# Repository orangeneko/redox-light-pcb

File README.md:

## About
Eagle version of PCB for [Redox keyboard](https://github.com/mattdibi/redox-keyboard) with RBG backlight (of each keys).

## PCB

## Hardware
* Cortex M3 STM32F103T8U
* SK6812 CMD 3535 Leds (similar with WS2812B)
* Cherry MX switches
* Kailh PCB sockets

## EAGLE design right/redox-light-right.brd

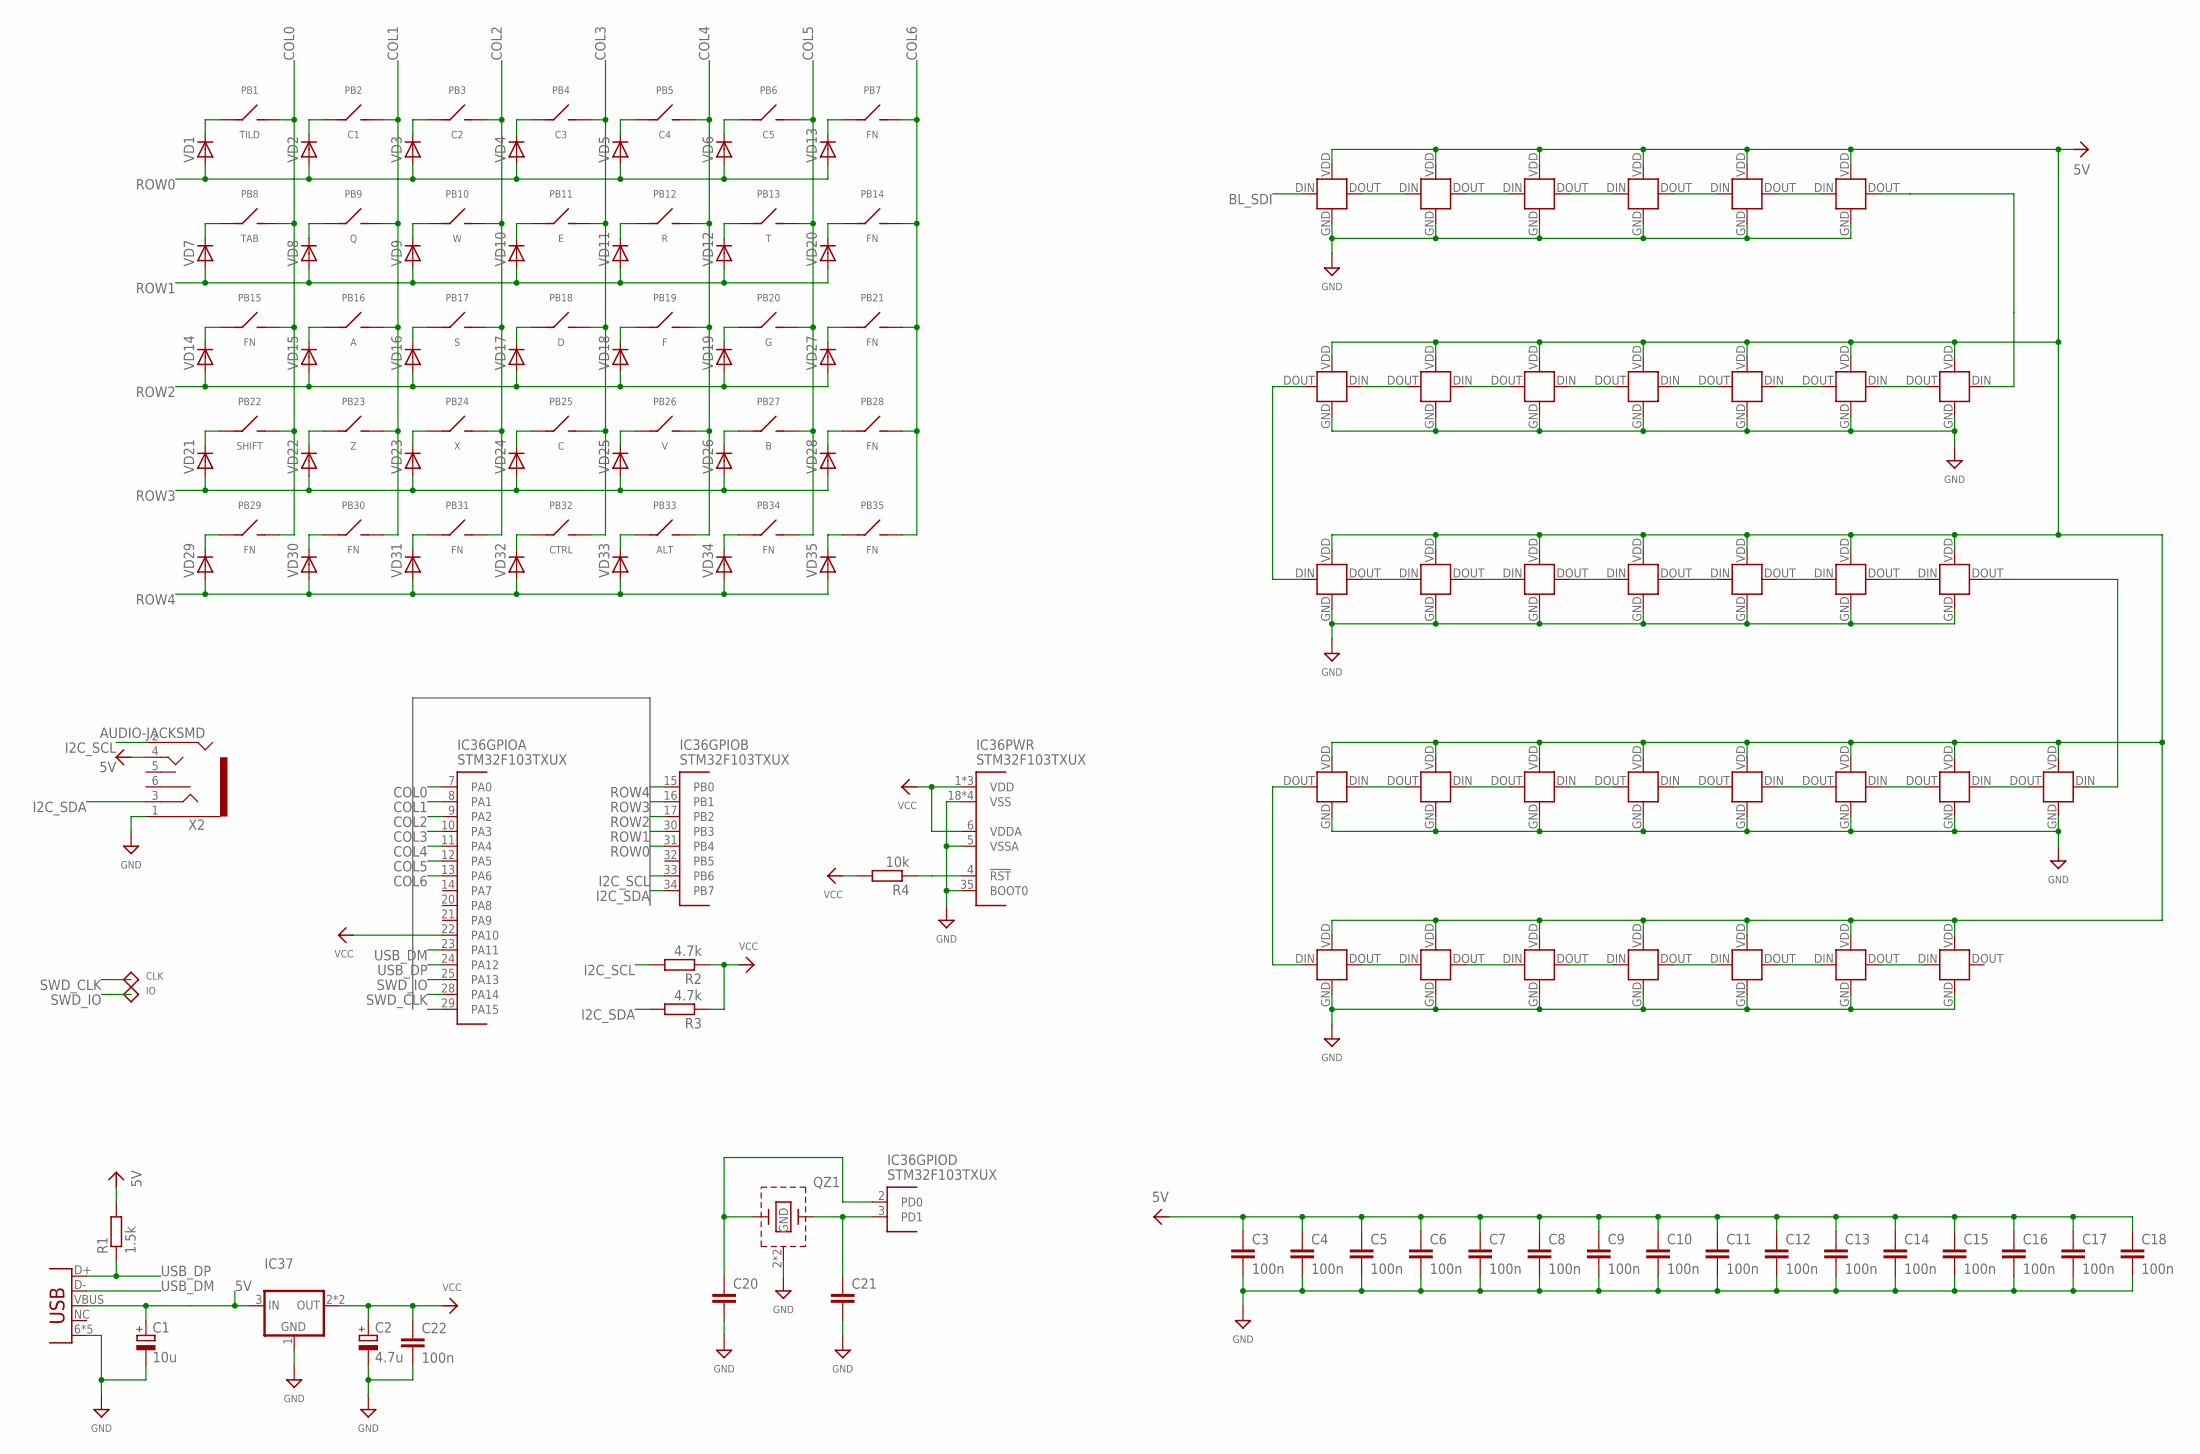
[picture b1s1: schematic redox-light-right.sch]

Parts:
C1: 10u; SMC_A
C2: 4.7u; SMC_A
C3, C4, C5, C6, C7, C8, C9, C10, C11, C12, C13, C14, C15, C16, C17, C18, C22: 100n; R0402
C20, C21: CAP0402; R0402
IC1, IC2, IC3, IC4, IC5, IC6, IC7, IC8, IC9, IC10, IC11, IC12, IC13, IC14, IC15, IC16, IC17, IC18, IC19, IC20, IC21, IC22, IC23, IC24, IC25, IC26, IC27, IC28, IC29, IC30, IC31, IC32, IC33, IC34, IC35: SK68XX-MINI
IC36: STM32F103TXUX; QFN-36
IC37: LM1117; SOT89
PB1: TILD; CHERRY-MX-KAILH
PB2: C1; CHERRY-MX-KAILH
PB3: C2; CHERRY-MX-KAILH
PB4: C3; CHERRY-MX-KAILH
PB5: C4; CHERRY-MX-KAILH
PB6: C5; CHERRY-MX-KAILH
PB7, PB14, PB15, PB21, PB28, PB29, PB30, PB31, PB34, PB35: FN; CHERRY-MX-KAILH
PB8: TAB; CHERRY-MX-KAILH
PB9: Q; CHERRY-MX-KAILH
PB10: W; CHERRY-MX-KAILH
PB11: E; CHERRY-MX-KAILH
PB12: R; CHERRY-MX-KAILH
PB13: T; CHERRY-MX-KAILH
PB16: A; CHERRY-MX-KAILH
PB17: S; CHERRY-MX-KAILH
PB18: D; CHERRY-MX-KAILH
PB19: F; CHERRY-MX-KAILH
PB20: G; CHERRY-MX-KAILH
PB22: SHIFT; CHERRY-MX-KAILH
PB23: Z; CHERRY-MX-KAILH
PB24: X; CHERRY-MX-KAILH
PB25: C; CHERRY-MX-KAILH
PB26: V; CHERRY-MX-KAILH
PB27: B; CHERRY-MX-KAILH
PB32: CTRL; CHERRY-MX-KAILH
PB33: ALT; CHERRY-MX-KAILH
QZ1: QUARTZ_GND3225; 3225
R1: 1.5k; R0402
R2, R3: 4.7k; R0402
R4: 10k; R0402
TP1: CLK; TP10R
TP2: IO; TP10R
VD1, VD2, VD3, VD4, VD5, VD6, VD7, VD8, VD9, VD10, VD11, VD12, VD13, VD14, VD15, VD16, VD17, VD18, VD19, VD20, VD21, VD22, VD23, VD24, VD25, VD26, VD27, VD28, VD29, VD30, VD31, VD32, VD33, VD34, VD35: DIODE-SOD123; SOD123
X1: USBMICRO_B; USB_MICROB
X2: AUDIO-JACKSMD; PJ-342

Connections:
5V: C1.+, C3.1, C4.1, C5.1, C6.1, C7.1, C8.1, C9.1, C10.1, C11.1, C12.1, C13.1, C14.1, C15.1, C16.1, C17.1, C18.1, IC1.VDD (VCC), IC2.VDD (VCC), IC3.VDD (VCC), IC4.VDD (VCC), IC5.VDD (VCC), IC6.VDD (VCC), IC7.VDD (VCC), IC8.VDD (VCC), IC9.VDD (VCC), IC10.VDD (VCC), IC11.VDD (VCC), IC12.VDD (VCC), IC13.VDD (VCC), IC14.VDD (VCC), IC15.VDD (VCC), IC16.VDD (VCC), IC17.VDD (VCC), IC18.VDD (VCC), IC19.VDD (VCC), IC20.VDD (VCC), IC21.VDD (VCC), IC22.VDD (VCC), IC23.VDD (VCC), IC24.VDD (VCC), IC25.VDD (VCC), IC26.VDD (VCC), IC27.VDD (VCC), IC28.VDD (VCC), IC29.VDD (VCC), IC30.VDD (VCC), IC31.VDD (VCC), IC32.VDD (VCC), IC33.VDD (VCC), IC34.VDD (VCC), IC35.VDD (VCC), IC37.3 (IN), R1.2, X1.VBUS, X2.4
BL_SDI: IC1.DIN, IC36.29 (PA15)
COL0: IC36.7 (PA0), PB1.2, PB8.2, PB15.2, PB22.2, PB29.2
COL1: IC36.8 (PA1), PB2.2, PB9.2, PB16.2, PB23.2, PB30.2
COL2: IC36.9 (PA2), PB3.2, PB10.2, PB17.2, PB24.2, PB31.2
COL3: IC36.10 (PA3), PB4.2, PB11.2, PB18.2, PB25.2, PB32.2
COL4: IC36.11 (PA4), PB5.2, PB12.2, PB19.2, PB26.2, PB33.2
COL5: IC36.12 (PA5), PB6.2, PB13.2, PB20.2, PB27.2, PB34.2
COL6: IC36.13 (PA6), PB7.2, PB14.2, PB21.2, PB28.2, PB35.2
GND: C1.-, C2.-, C3.2, C4.2, C5.2, C6.2, C7.2, C8.2, C9.2, C10.2, C11.2, C12.2, C13.2, C14.2, C15.2, C16.2, C17.2, C18.2, C20.2, C21.2, C22.2, IC1.GND, IC2.GND, IC3.GND, IC4.GND, IC5.GND, IC6.GND, IC7.GND, IC8.GND, IC9.GND, IC10.GND, IC11.GND, IC12.GND, IC13.GND, IC14.GND, IC15.GND, IC16.GND, IC17.GND, IC18.GND, IC19.GND, IC20.GND, IC21.GND, IC22.GND, IC23.GND, IC24.GND, IC25.GND, IC26.GND, IC27.GND, IC28.GND, IC29.GND, IC30.GND, IC31.GND, IC32.GND, IC33.GND, IC34.GND, IC35.GND, IC36.5 (VSSA), IC36.18 (VSS), IC36.26 (VSS), IC36.35 (BOOT0), IC36.36 (VSS), IC36.PGND (VSS), IC37.1 (GND), QZ1.2 (GND), QZ1.4 (GND), X1.6 (GND), X1.7 (GND), X1.8 (GND), X1.9 (GND), X1.GND, X2.1
I2C_SCL: IC36.33 (PB6), R2.2, X2.2
I2C_SDA: IC36.34 (PB7), R3.2, X2.3
unnamed: IC1.DOUT, IC2.DIN
unnamed: IC2.DOUT, IC3.DIN
unnamed: IC3.DOUT, IC4.DIN
unnamed: IC4.DOUT, IC5.DIN
unnamed: IC5.DOUT, IC6.DIN
unnamed: IC7.DOUT, IC8.DIN
unnamed: PB1.1, VD1.C
unnamed: IC21.DOUT, IC22.DIN
unnamed: IC22.DOUT, IC23.DIN
unnamed: IC23.DOUT, IC24.DIN
unnamed: IC24.DOUT, IC25.DIN
unnamed: IC25.DOUT, IC26.DIN
unnamed: IC8.DOUT, IC9.DIN
unnamed: IC13.DOUT, IC14.DIN
unnamed: IC26.DOUT, IC27.DIN
unnamed: IC20.DOUT, IC21.DIN
unnamed: PB4.1, VD4.C
unnamed: PB3.1, VD3.C
unnamed: PB5.1, VD5.C
unnamed: PB6.1, VD6.C
unnamed: PB2.1, VD2.C
unnamed: PB7.1, VD13.C
unnamed: C20.1, IC36.2 (PD0), QZ1.3 (2)
unnamed: PB8.1, VD7.C
unnamed: PB9.1, VD8.C
unnamed: PB10.1, VD9.C
unnamed: PB11.1, VD10.C
unnamed: PB12.1, VD11.C
unnamed: PB13.1, VD12.C
unnamed: PB14.1, VD20.C
unnamed: C21.1, IC36.3 (PD1), QZ1.1
unnamed: IC9.DOUT, IC10.DIN
unnamed: IC10.DOUT, IC11.DIN
unnamed: IC11.DOUT, IC12.DIN
unnamed: IC36.4 (!RST), R4.1
unnamed: IC12.DOUT, IC13.DIN
unnamed: IC6.DOUT, IC7.DIN
unnamed: IC14.DOUT, IC15.DIN
unnamed: IC15.DOUT, IC16.DIN
unnamed: IC16.DOUT, IC17.DIN
unnamed: IC17.DOUT, IC18.DIN
unnamed: IC18.DOUT, IC19.DIN
unnamed: IC19.DOUT, IC20.DIN
unnamed: PB15.1, VD14.C
unnamed: PB16.1, VD15.C
unnamed: PB17.1, VD16.C
unnamed: PB18.1, VD17.C
unnamed: PB19.1, VD18.C
unnamed: PB20.1, VD19.C
unnamed: IC27.DOUT, IC28.DIN
unnamed: IC29.DOUT, IC30.DIN
unnamed: PB22.1, VD21.C
unnamed: PB23.1, VD22.C
unnamed: PB29.1, VD29.C
unnamed: PB30.1, VD30.C
unnamed: PB24.1, VD23.C
unnamed: PB25.1, VD24.C
unnamed: PB26.1, VD25.C
unnamed: PB27.1, VD26.C
unnamed: PB21.1, VD27.C
unnamed: PB28.1, VD28.C
unnamed: PB31.1, VD31.C
unnamed: PB32.1, VD32.C
unnamed: PB33.1, VD33.C
unnamed: PB34.1, VD34.C
unnamed: PB35.1, VD35.C
unnamed: IC30.DOUT, IC31.DIN
unnamed: IC31.DOUT, IC32.DIN
unnamed: IC32.DOUT, IC33.DIN
unnamed: IC33.DOUT, IC34.DIN
unnamed: IC34.DOUT, IC35.DIN
unnamed: IC28.DOUT, IC29.DIN
ROW0: IC36.31 (PB4), VD1.A, VD2.A, VD3.A, VD4.A, VD5.A, VD6.A, VD13.A
ROW1: IC36.30 (PB3), VD7.A, VD8.A, VD9.A, VD10.A, VD11.A, VD12.A, VD20.A
ROW2: IC36.17 (PB2), VD14.A, VD15.A, VD16.A, VD17.A, VD18.A, VD19.A, VD27.A
ROW3: IC36.16 (PB1), VD21.A, VD22.A, VD23.A, VD24.A, VD25.A, VD26.A, VD28.A
ROW4: IC36.15 (PB0), VD29.A, VD30.A, VD31.A, VD32.A, VD33.A, VD34.A, VD35.A
SWD_CLK: IC36.28 (PA14), TP1.TP
SWD_IO: IC36.25 (PA13), TP2.TP
USB_DM: IC36.23 (PA11), X1.D-
USB_DP: IC36.24 (PA12), R1.1, X1.D+
VCC: C2.+, C22.1, IC36.1 (VDD), IC36.6 (VDDA), IC36.19 (VDD), IC36.22 (PA10), IC36.27 (VDD), IC37.2 (OUT), IC37.4 (OUT), R2.1, R3.1, R4.2

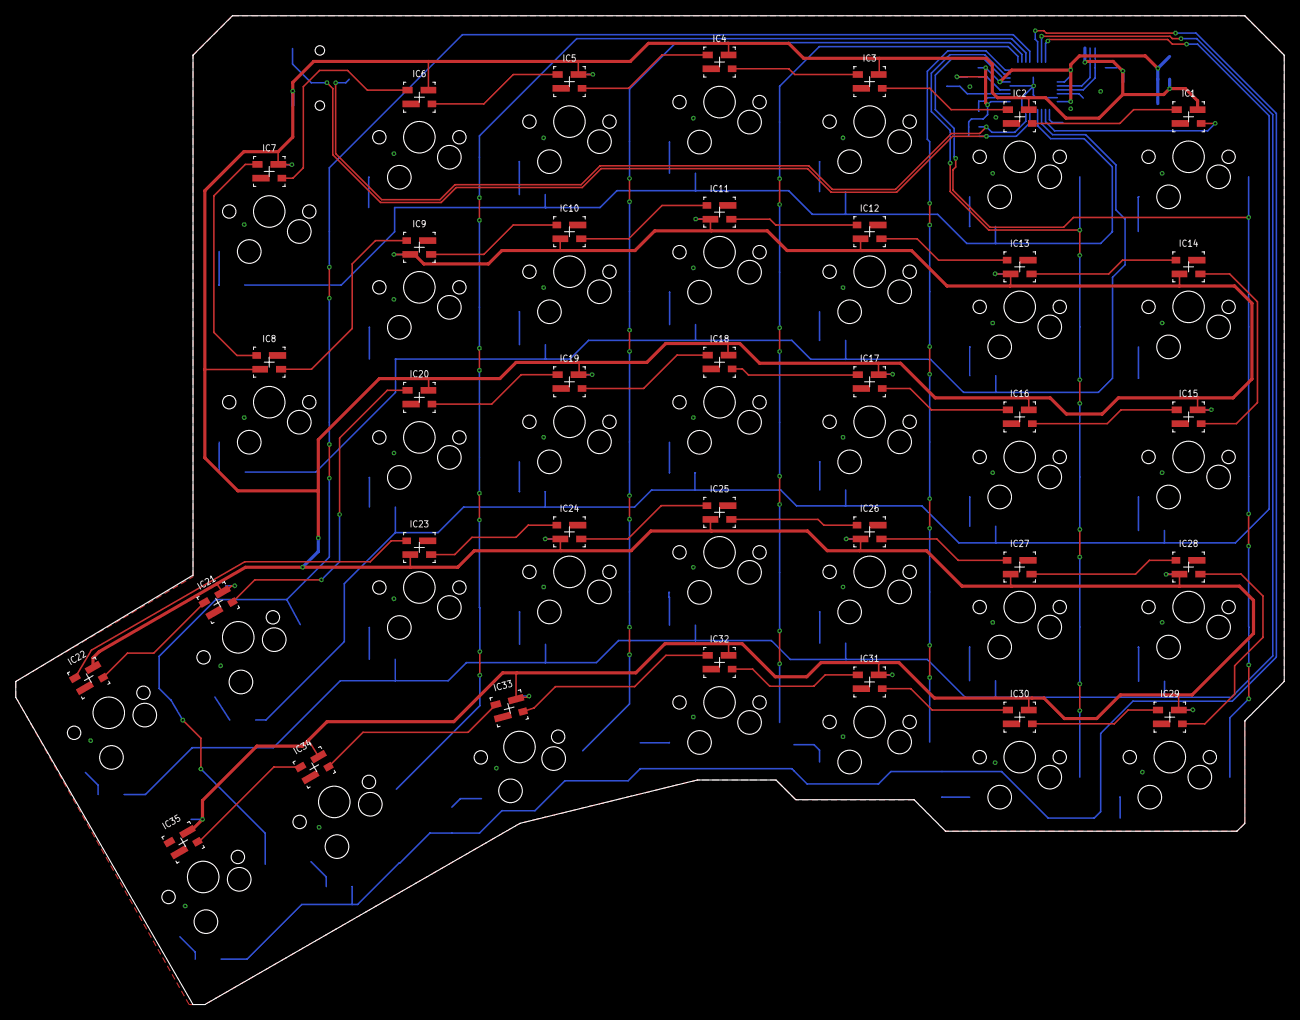
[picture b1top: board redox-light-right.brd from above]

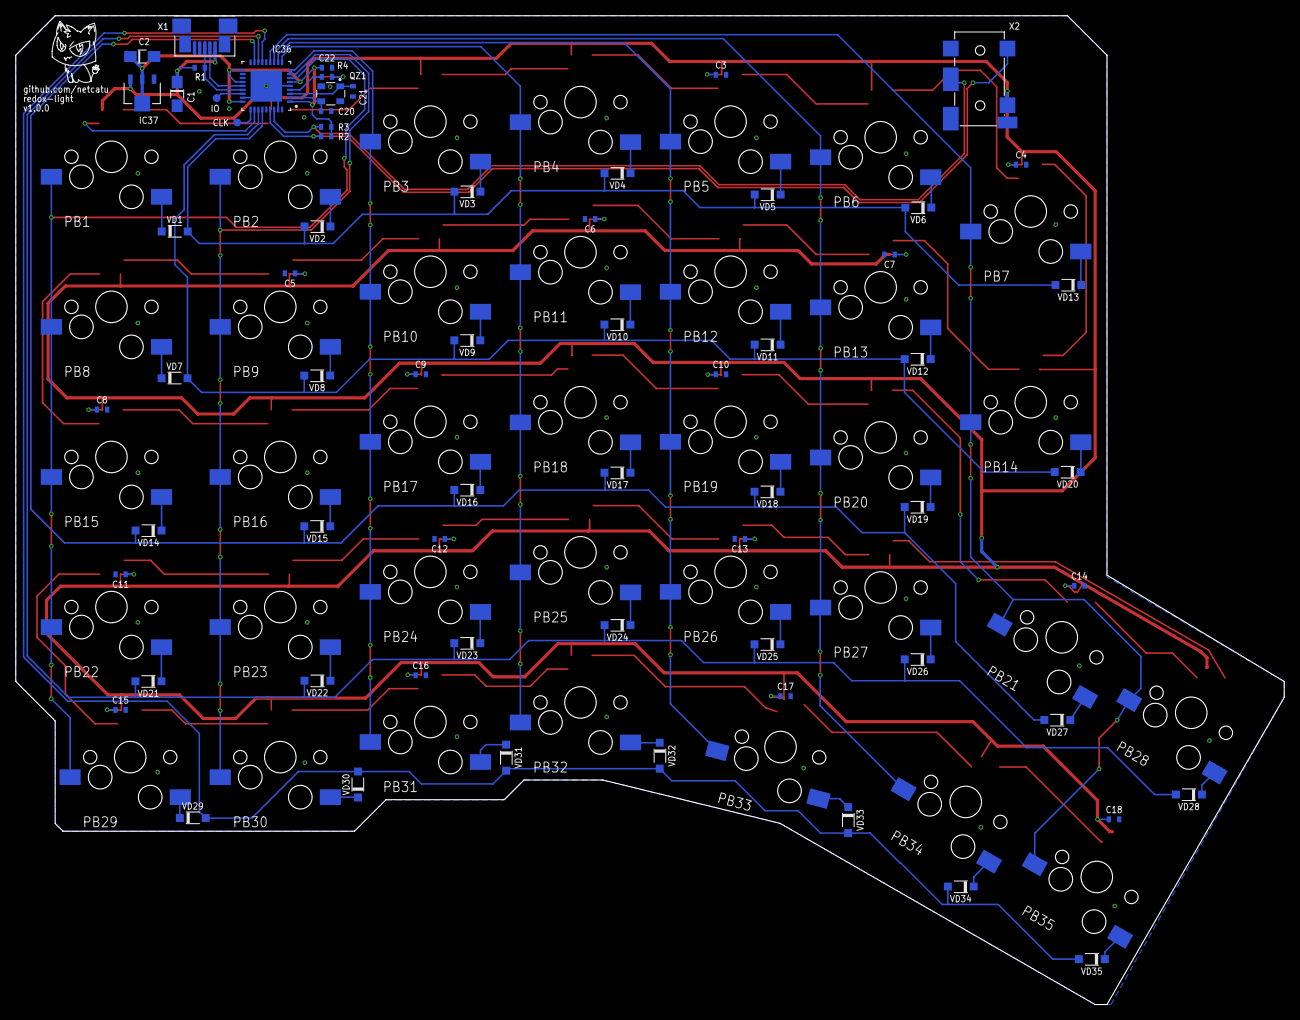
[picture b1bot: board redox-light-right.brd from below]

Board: 2 copper layers, 161.0 x 125.5 mm, 138 parts (68 on the bottom side), 94 nets.

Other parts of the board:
U$1: LOGO2

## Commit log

2018-07-30 schematic, board components alignment
2018-07-31 layout template
2018-08-21 aligned buttons, board layout completed
2018-08-23 layout, outline, silk update
2018-08-23 make schematic more simply, added SWD connector
2018-08-27 silk layer update
2018-09-10 replace swd connector with tps, move files
2018-09-10 added right part
2018-09-10 some improoves
2018-09-13 drc warn fixes
2018-09-13 first release, updated docs, added gerbers
2018-12-26 lm1117 pkg fix
